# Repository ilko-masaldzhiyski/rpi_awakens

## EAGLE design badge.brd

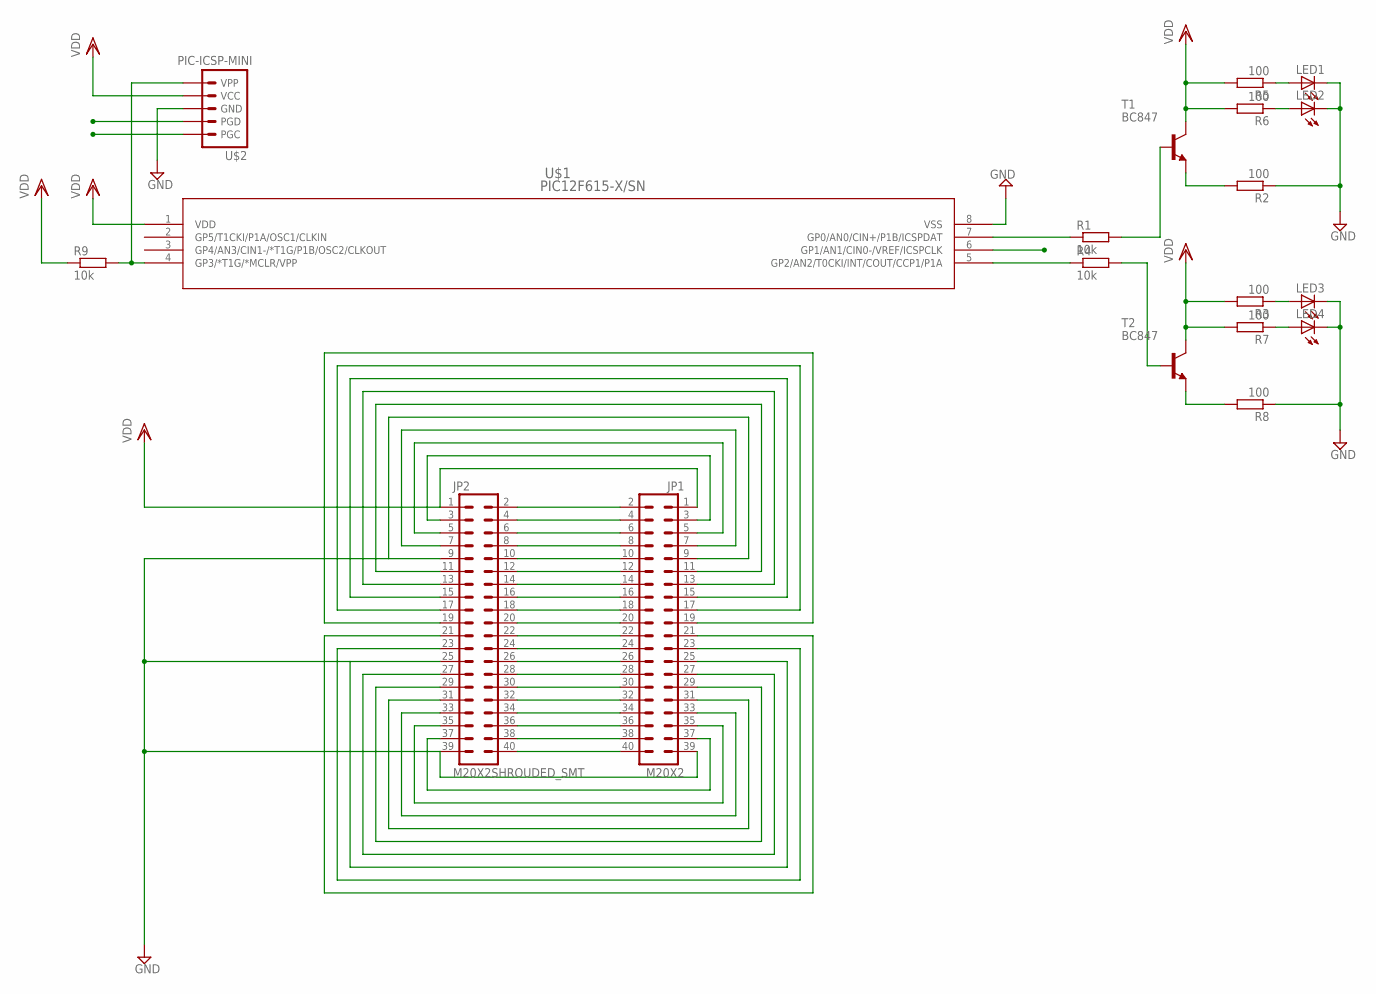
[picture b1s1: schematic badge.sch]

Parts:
JP1: M20X2; 2X20
JP2: M20X2SHROUDED_SMT; 2X20_SHROUDED_SMT
LED1, LED2, LED3, LED4: LEDCHIPLED_0805; CHIPLED_0805
R1, R4, R9: 10k; R0805
R2, R3, R5, R6, R7, R8: 100; R0805
T1, T2: BC847; SOT23
U$1: PIC12F615-X/SN; SOIC8-N_MC
U$2: PIC-ICSP-MINI

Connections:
GND: JP1.6, JP1.9, JP1.14, JP1.20, JP1.25, JP1.30, JP1.34, JP1.39, JP2.6, JP2.9, JP2.14, JP2.20, JP2.25, JP2.30, JP2.34, JP2.39, LED1.C, LED2.C, LED3.C, LED4.C, R2.1, R8.1, U$1.8 (VSS), U$2.3 (GND)
ICSPCLK: U$1.6 (GP1/AN1/CIN0-/VREF/ICSPCLK), U$2.5 (PGC)
ICSPDAT: R1.1, U$1.7 (GP0/AN0/CIN+/P1B/ICSPDAT), U$2.4 (PGD)
unnamed: R4.1, U$1.5 (GP2/AN2/T0CKI/INT/COUT/CCP1/P1A)
unnamed: R9.2, U$1.4 (GP3/*T1G/*MCLR/VPP), U$2.1 (VPP)
unnamed: R4.2, T2.1 (B)
unnamed: LED1.A, R5.1
unnamed: R2.2, T1.2 (E)
unnamed: R1.2, T1.1 (B)
unnamed: LED2.A, R6.1
unnamed: LED3.A, R3.1
unnamed: LED4.A, R7.1
unnamed: R8.2, T2.2 (E)
unnamed: JP1.2, JP2.2
unnamed: JP1.4, JP2.4
unnamed: JP1.8, JP2.8
unnamed: JP1.10, JP2.10
unnamed: JP1.12, JP2.12
unnamed: JP1.16, JP2.16
unnamed: JP1.18, JP2.18
unnamed: JP1.22, JP2.22
unnamed: JP1.24, JP2.24
unnamed: JP1.26, JP2.26
unnamed: JP1.28, JP2.28
unnamed: JP1.32, JP2.32
unnamed: JP1.36, JP2.36
unnamed: JP1.38, JP2.38
unnamed: JP1.40, JP2.40
unnamed: JP1.3, JP2.3
unnamed: JP1.5, JP2.5
unnamed: JP1.7, JP2.7
unnamed: JP1.11, JP2.11
unnamed: JP1.13, JP2.13
unnamed: JP1.15, JP2.15
unnamed: JP1.17, JP2.17
unnamed: JP1.19, JP2.19
unnamed: JP1.37, JP2.37
unnamed: JP1.35, JP2.35
unnamed: JP1.33, JP2.33
unnamed: JP1.31, JP2.31
unnamed: JP1.29, JP2.29
unnamed: JP1.27, JP2.27
unnamed: JP1.23, JP2.23
unnamed: JP1.21, JP2.21
VDD: JP1.1, JP2.1, R3.2, R5.2, R6.2, R7.2, R9.1, T1.3 (C), T2.3 (C), U$1.1 (VDD), U$2.2 (VCC)

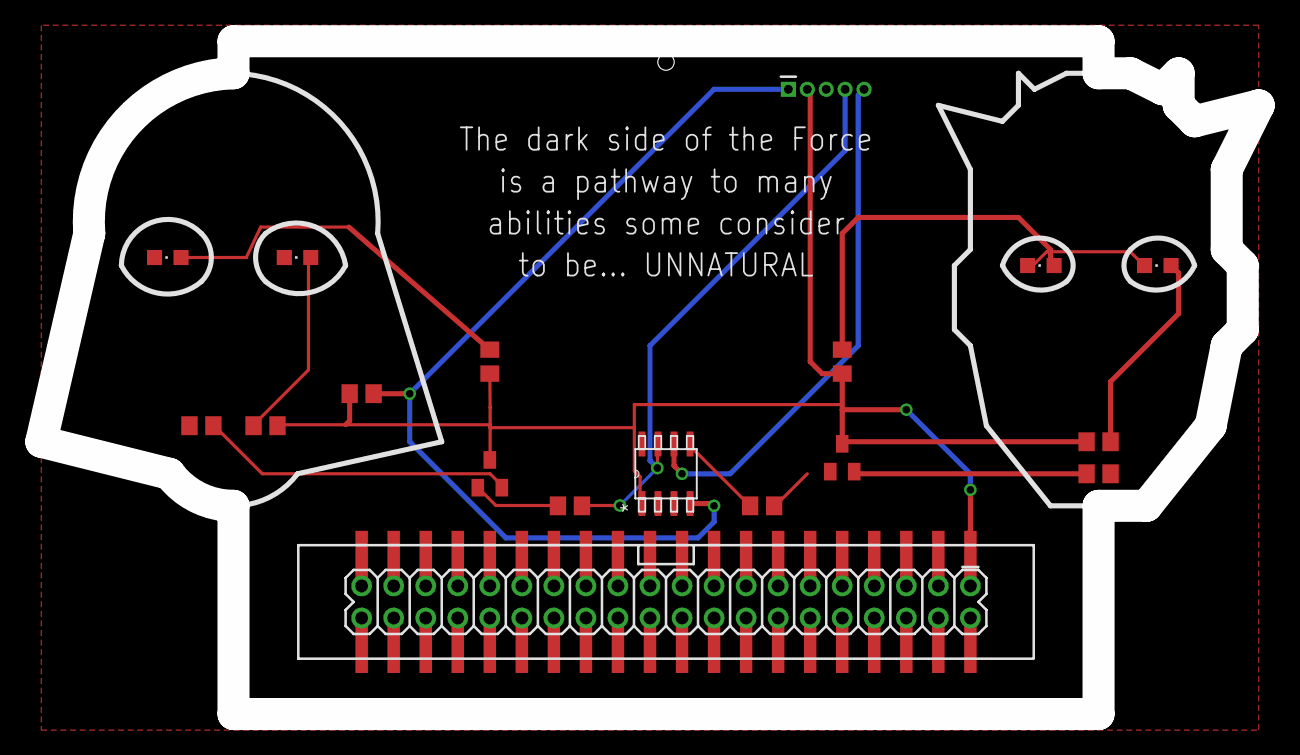
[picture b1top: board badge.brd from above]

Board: 2 copper layers, 96.5 x 53.3 mm, 19 parts (0 on the bottom side), 45 nets.

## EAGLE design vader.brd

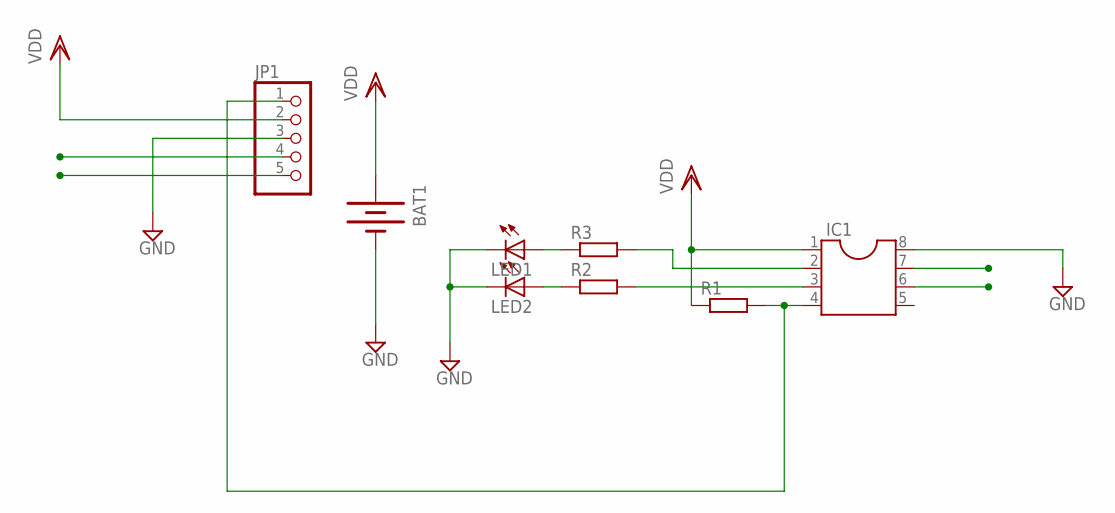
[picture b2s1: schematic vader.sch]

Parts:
BAT1: BATTERY20PTH; BATTCOM_20MM_PTH
IC1: DIL8S; SOCKET-08
JP1: PINHD-1X5; 1X05
LED1, LED2: LED3MM
R1, R2, R3: R-EU_0204/7; 0204/7

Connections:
GND: BAT1.2 (-), IC1.8, JP1.3, LED1.K (C), LED2.K (C)
ICSPCLK: IC1.6, JP1.5
ICSPDAT: IC1.7, JP1.4
unnamed: IC1.4, JP1.1, R1.2
unnamed: IC1.3, R2.2
unnamed: IC1.2, R3.2
unnamed: LED1.A, R3.1
unnamed: LED2.A, R2.1
VDD: BAT1.1 (+), IC1.1, JP1.2, R1.1

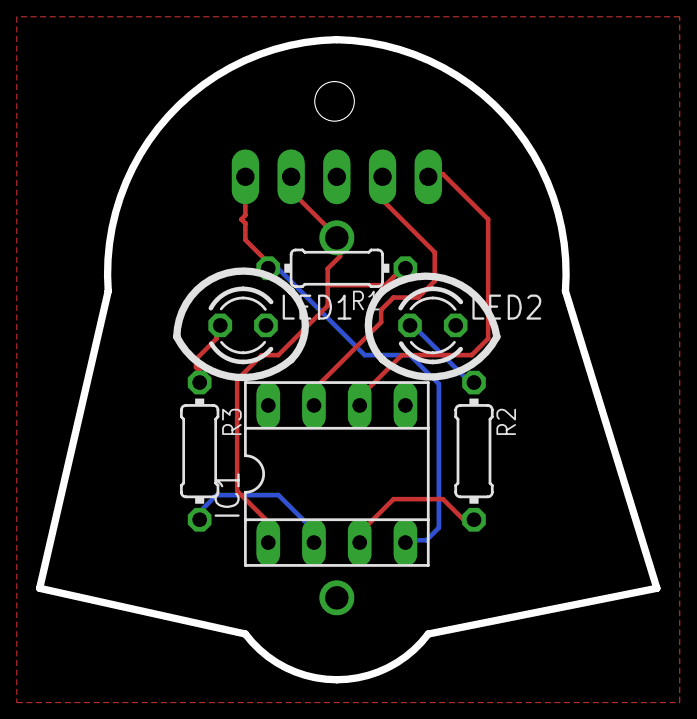
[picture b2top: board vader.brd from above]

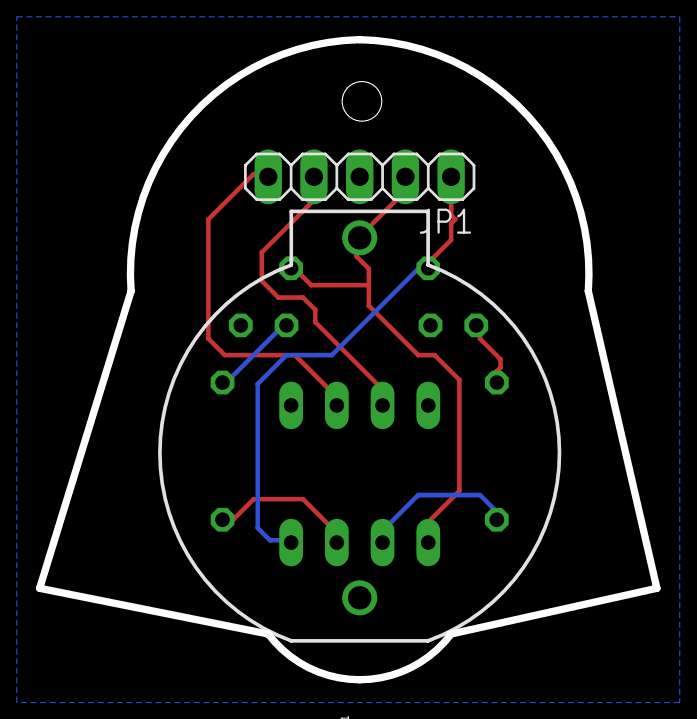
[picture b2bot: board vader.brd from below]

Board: 2 copper layers, 34.3 x 35.6 mm, 8 parts (2 on the bottom side), 9 nets.

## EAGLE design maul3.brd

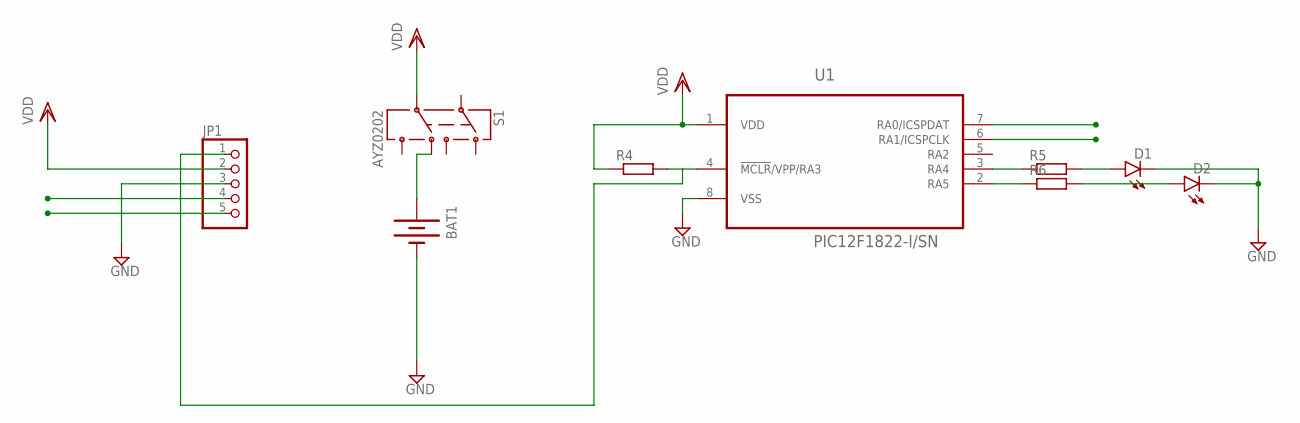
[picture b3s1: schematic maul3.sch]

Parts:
BAT1: BATTERYFOB; BATTERY_20MM_PTH_COMPACT
D1, D2: LED1206; LED-1206
JP1: PINHD-1X5; 1X05
R4, R5, R6: R-EU_R1206; R1206
S1: AYZ0202
U1: PIC12F1822-I/SN; SOIC127P600X175-8N

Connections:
GND: BAT1.2 (-), D1.C, D2.C, JP1.3, U1.8 (VSS)
ICSPCLK: JP1.5, U1.6 (RA1/ICSPCLK)
ICSPDAT: JP1.4, U1.7 (RA0/ICSPDAT)
unnamed: BAT1.1 (+), S1.6 (4)
unnamed: R6.1, U1.2 (RA5)
unnamed: R5.1, U1.3 (RA4)
unnamed: D2.A, R6.2
unnamed: D1.A, R5.2
VDD: JP1.2, R4.1, S1.5, U1.1 (VDD)
VPP: JP1.1, R4.2, U1.4 (!MCLR!/VPP/RA3)

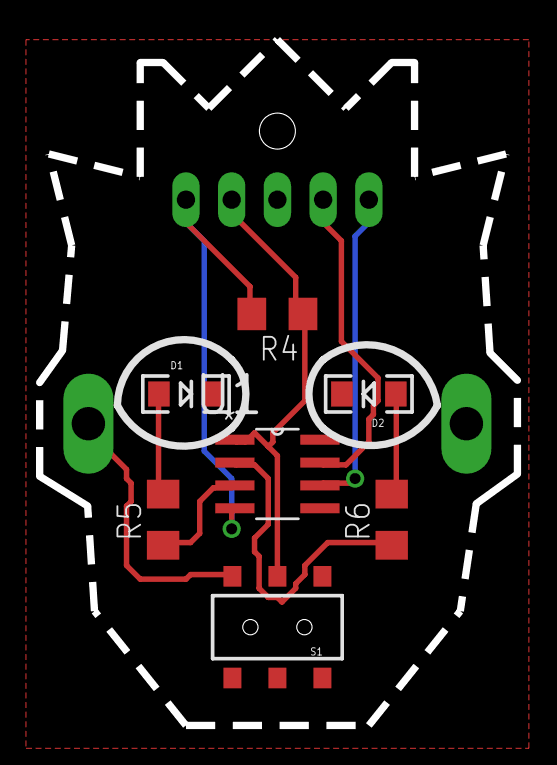
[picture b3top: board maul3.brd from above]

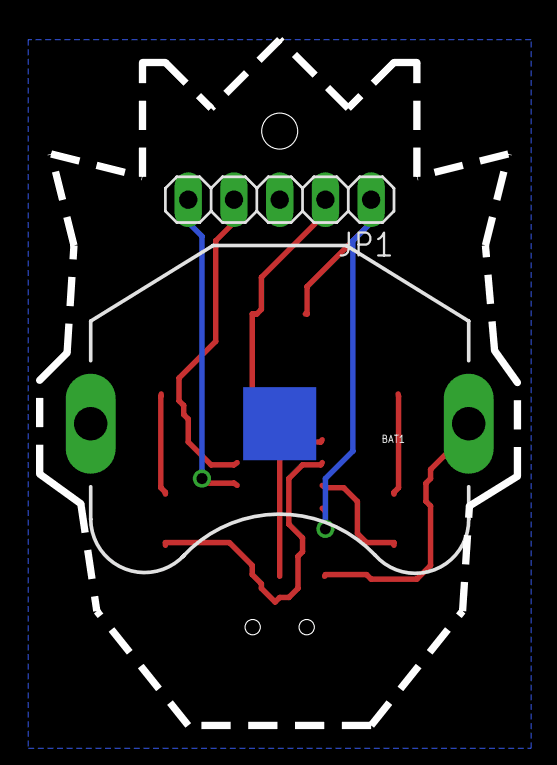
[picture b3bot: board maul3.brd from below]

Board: 2 copper layers, 26.5 x 38.1 mm, 9 parts (2 on the bottom side), 10 nets.

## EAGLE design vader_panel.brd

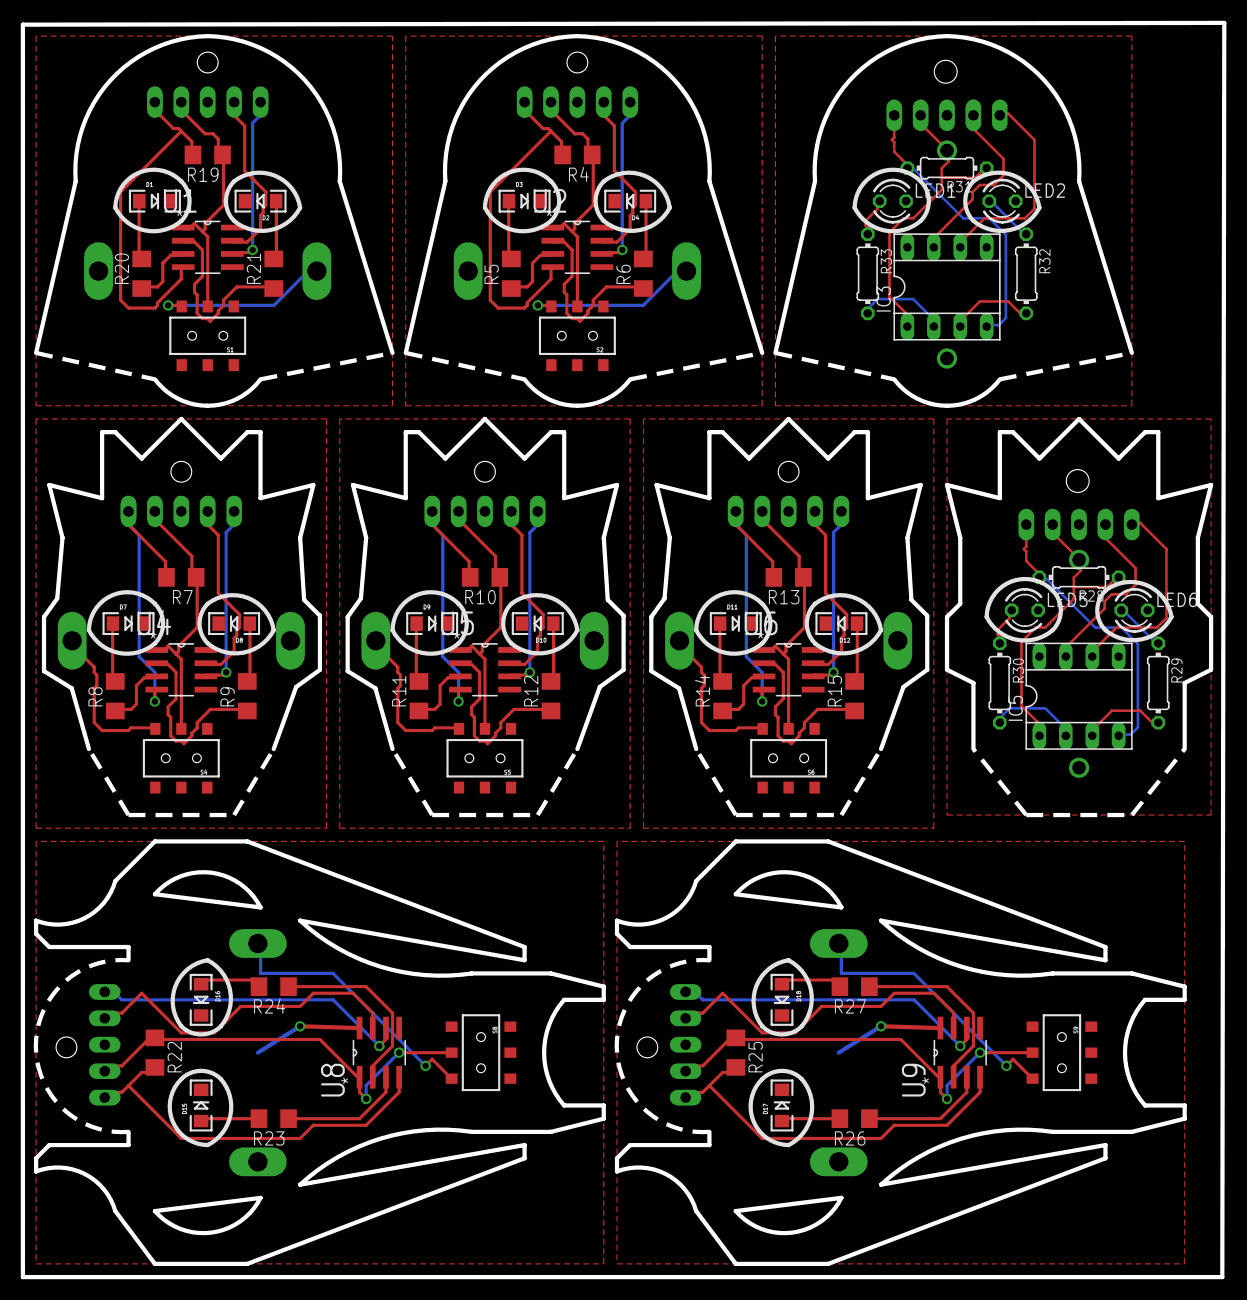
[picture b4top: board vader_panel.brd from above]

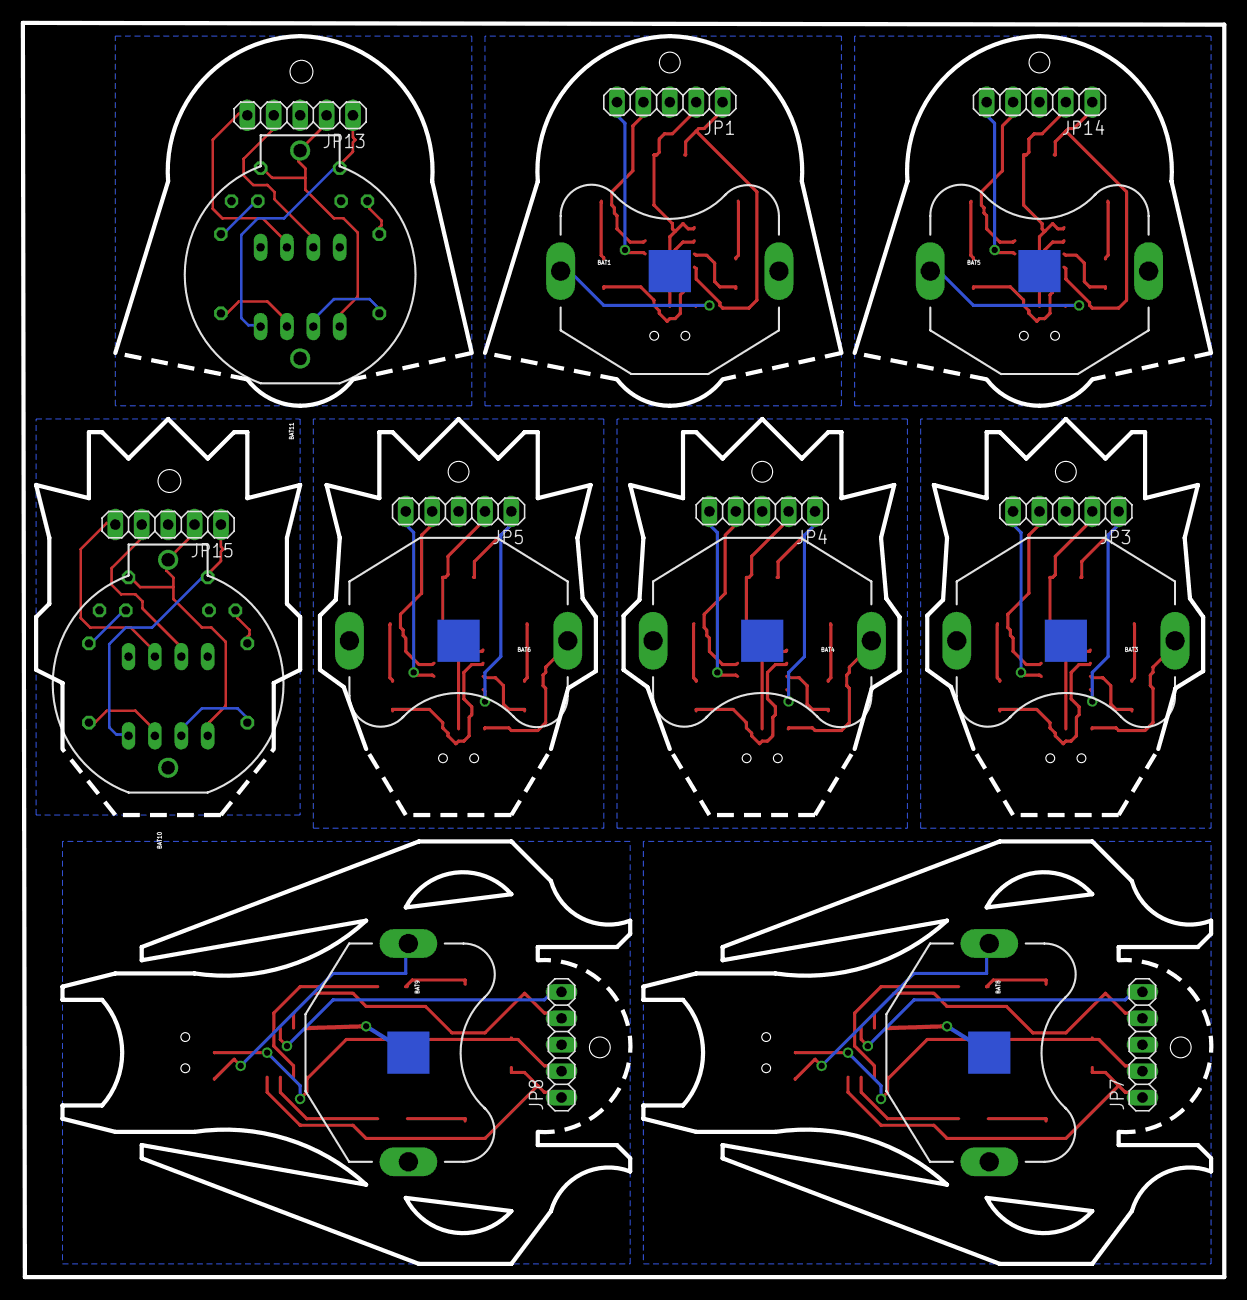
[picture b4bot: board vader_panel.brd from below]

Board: 2 copper layers, 115.6 x 120.6 mm, 79 parts (18 on the bottom side), 88 nets.

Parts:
BAT1, BAT3, BAT4, BAT5, BAT6, BAT8, BAT9: BATTERY_20MM_PTH_COMPACT
BAT10, BAT11: BATTCOM_20MM_PTH
D1, D2, D3, D4, D7, D8, D9, D10, D11, D12, D15, D16, D17, D18: LED-1206
IC3, IC5: SOCKET-08
JP1, JP3, JP4, JP5, JP7, JP8, JP13, JP14, JP15: 1X05
LED1, LED2, LED5, LED6: LED3MM
R4, R5, R6, R7, R8, R9, R10, R11, R12, R13, R14, R15, R19, R20, R21, R22, R23, R24, R25, R26, R27: R1206
R28, R29, R30, R31, R32, R33: 0204/7
S1, S2, S4, S5, S6, S8, S9: AYZ0202
U1, U2, U4, U5, U6, U8, U9: PIC12F1822-I/SN; SOIC127P600X175-8N

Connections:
GND: BAT1.2, D3.C, D4.C, JP1.3, U2.8
GND2: BAT3.2, D7.C, D8.C, JP3.3, U4.8
GND3: BAT4.2, D9.C, D10.C, JP4.3, U5.8
GND4: BAT5.2, D1.C, D2.C, JP14.3, U1.8
GND5: BAT6.2, D11.C, D12.C, JP5.3, U6.8
GND7: BAT8.2, D15.C, D16.C, JP7.3, U8.8
GND8: BAT9.2, D17.C, D18.C, JP8.3, U9.8
GND9: BAT10.2, IC5.8, JP15.3, LED5.K, LED6.K
GND10: BAT11.2, IC3.8, JP13.3, LED1.K, LED2.K
ICSPCLK: JP1.5, U2.6
ICSPCLK2: JP3.5, U4.6
ICSPCLK3: JP4.5, U5.6
ICSPCLK4: JP14.5, U1.6
ICSPCLK5: JP5.5, U6.6
ICSPCLK7: JP7.5, U8.6
ICSPCLK8: JP8.5, U9.6
ICSPCLK9: IC5.6, JP15.5
ICSPCLK10: IC3.6, JP13.5
ICSPDAT: JP1.4, U2.7
ICSPDAT2: JP3.4, U4.7
ICSPDAT3: JP4.4, U5.7
ICSPDAT4: JP14.4, U1.7
ICSPDAT5: JP5.4, U6.7
ICSPDAT7: JP7.4, U8.7
ICSPDAT8: JP8.4, U9.7
ICSPDAT9: IC5.7, JP15.4
ICSPDAT10: IC3.7, JP13.4
unnamed: BAT1.1, S2.6
unnamed: R6.1, U2.2
unnamed: R5.1, U2.3
unnamed: D4.A, R6.2
unnamed: D3.A, R5.2
unnamed: R9.1, U4.2
unnamed: R8.1, U4.3
unnamed: D8.A, R9.2
unnamed: D7.A, R8.2
unnamed: BAT3.1, S4.6
unnamed: R12.1, U5.2
unnamed: R11.1, U5.3
unnamed: D10.A, R12.2
unnamed: D9.A, R11.2
unnamed: BAT4.1, S5.6
unnamed: R15.1, U6.2
unnamed: R21.1, U1.2
unnamed: R20.1, U1.3
unnamed: D2.A, R21.2
unnamed: D1.A, R20.2
unnamed: BAT5.1, S1.6
unnamed: R14.1, U6.3
unnamed: D12.A, R15.2
unnamed: D11.A, R14.2
unnamed: BAT6.1, S6.6
unnamed: R24.1, U8.2
unnamed: R23.1, U8.3
unnamed: D16.A, R24.2
unnamed: D15.A, R23.2
unnamed: BAT8.1, S8.6
unnamed: R27.1, U9.2
unnamed: R26.1, U9.3
unnamed: D18.A, R27.2
unnamed: D17.A, R26.2
unnamed: BAT9.1, S9.6
unnamed: IC5.4, JP15.1, R28.2
unnamed: IC5.3, R29.2
unnamed: IC5.2, R30.2
unnamed: LED5.A, R30.1
unnamed: LED6.A, R29.1
unnamed: IC3.4, JP13.1, R31.2
unnamed: IC3.3, R32.2
unnamed: IC3.2, R33.2
unnamed: LED1.A, R33.1
unnamed: LED2.A, R32.1
VDD: JP1.2, R4.1, S2.5, U2.1
VDD2: JP3.2, R7.1, S4.5, U4.1
VDD3: JP4.2, R10.1, S5.5, U5.1
VDD4: JP14.2, R19.1, S1.5, U1.1
VDD5: JP5.2, R13.1, S6.5, U6.1
VDD7: JP7.2, R22.1, S8.5, U8.1
VDD8: JP8.2, R25.1, S9.5, U9.1
VDD9: BAT10.1, IC5.1, JP15.2, R28.1
VDD10: BAT11.1, IC3.1, JP13.2, R31.1
VPP: JP14.1, R19.2, U1.4
VPP1: JP1.1, R4.2, U2.4
VPP3: JP3.1, R7.2, U4.4
VPP4: JP4.1, R10.2, U5.4
VPP5: JP5.1, R13.2, U6.4
VPP7: JP7.1, R22.2, U8.4
VPP8: JP8.1, R25.2, U9.4

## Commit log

2017-05-09 Commit2
2023-04-01 Update README
    Make sure the readme is not blank and makes sense

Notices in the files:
parts and their libraries:
SparkFun-Connectors: Licensing: Creative Commons ShareAlike 4.0 International - https://creativecommons.org/licenses/by-sa/4.0
